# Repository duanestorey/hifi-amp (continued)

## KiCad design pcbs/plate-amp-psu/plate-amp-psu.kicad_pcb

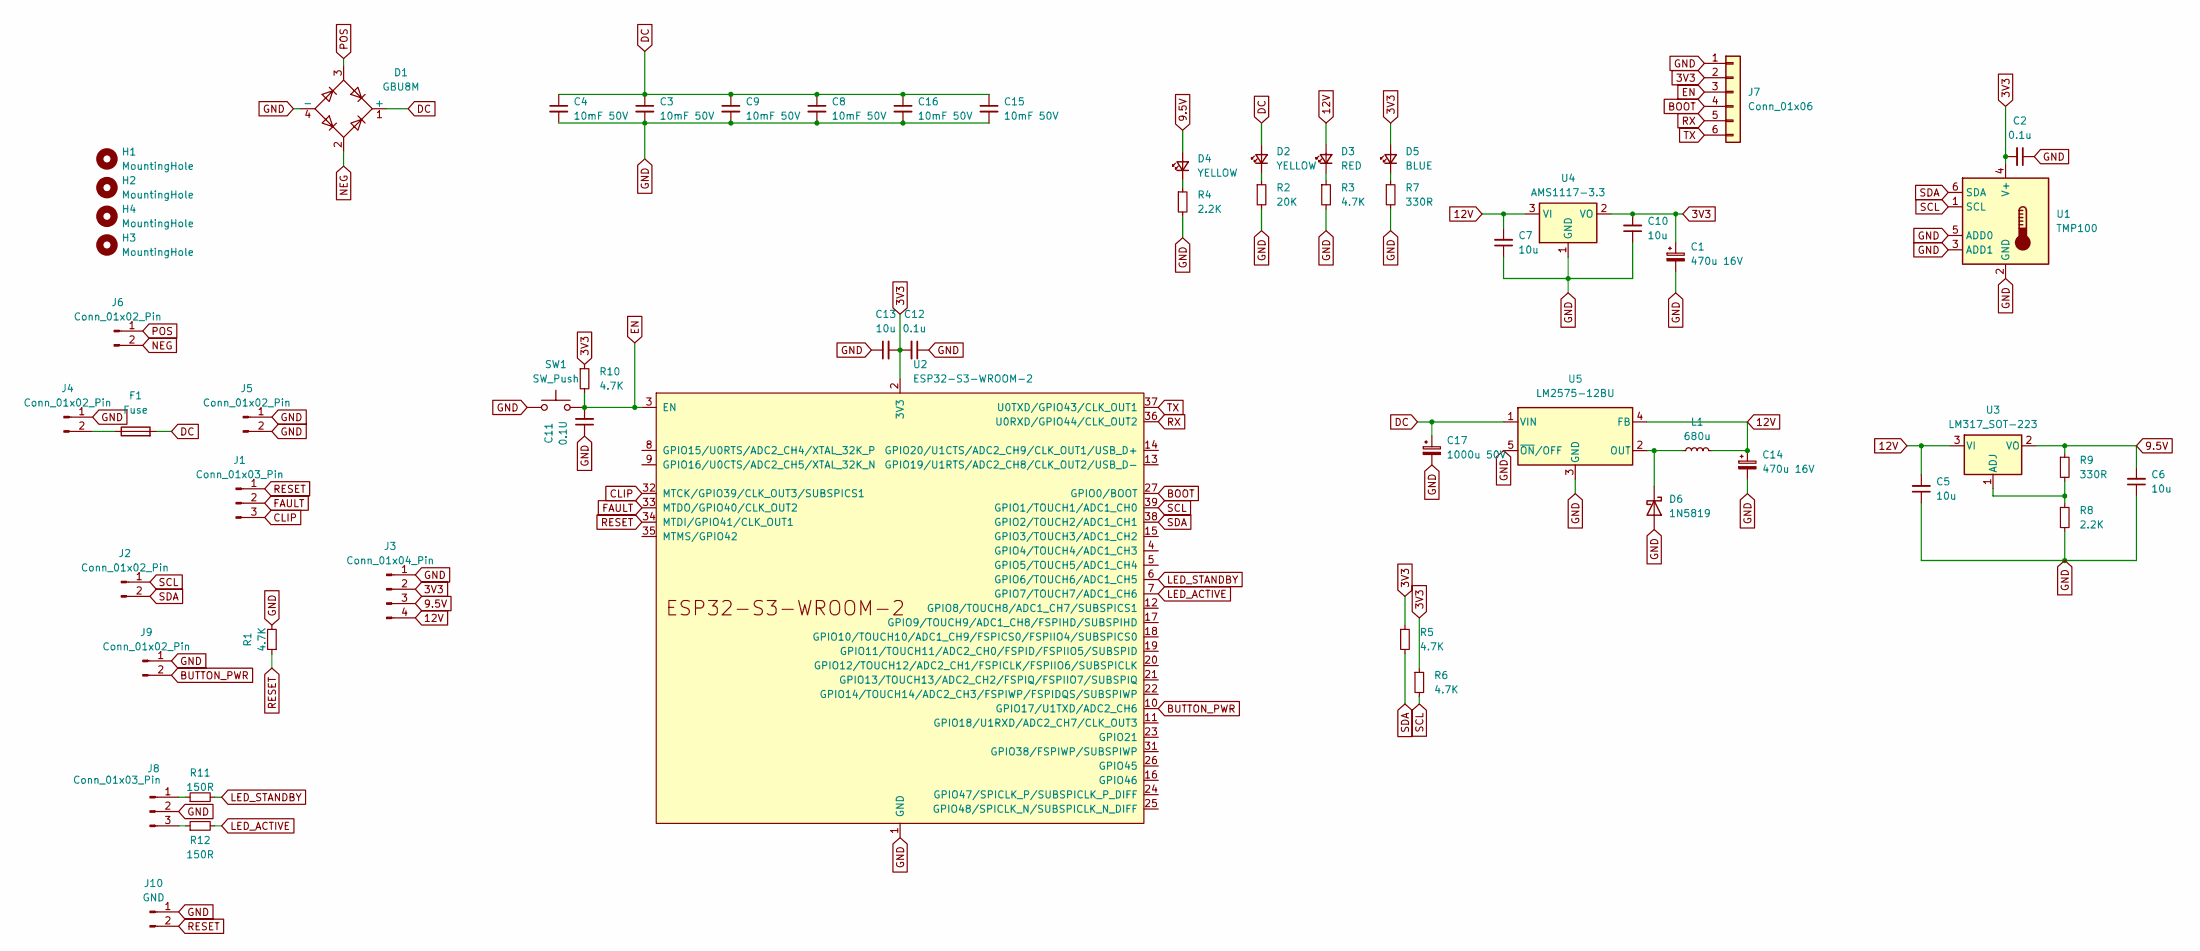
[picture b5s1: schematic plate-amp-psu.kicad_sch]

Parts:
C1, C14: 470u 16V; CP_Radial_D8.0mm_P3.50mm
C2, C12: 0.1u; C_0805_2012Metric_Pad1.18x1.45mm_HandSolder
C3, C4, C8, C9, C15, C16: 10mF 50V; CP_Radial_D25.0mm_P10.00mm_SnapIn
C5, C6, C7, C10, C13: 10u; C_1206_3216Metric_Pad1.33x1.80mm_HandSolder
C11: 0.1U; C_0805_2012Metric_Pad1.18x1.45mm_HandSolder
C17: 1000u 50V; CP_Radial_D12.5mm_P5.00mm
D1: GBU8M; Diode_Bridge_Vishay_GBU
D2, D4: YELLOW; LED_0805_2012Metric_Pad1.15x1.40mm_HandSolder
D3: RED; LED_0805_2012Metric_Pad1.15x1.40mm_HandSolder
D5: BLUE; LED_0805_2012Metric_Pad1.15x1.40mm_HandSolder
D6: 1N5819; D_DO-41_SOD81_P7.62mm_Horizontal; Mouser 863-MBR150RLG
F1: Fuse; Aliexpress Fuse 5x20
H1, H2, H3, H4: MountingHole; MountingHole_3.2mm_M3_DIN965_Pad_TopBottom
J1, J8: Conn_01x03_Pin; JST_PH_B3B-PH-K_1x03_P2.00mm_Vertical
J2, J9: Conn_01x02_Pin; JST_PH_B2B-PH-K_1x02_P2.00mm_Vertical
J3: Conn_01x04_Pin; JST_PH_B4B-PH-K_1x04_P2.00mm_Vertical
J4, J5: Conn_01x02_Pin; JST_VH_B2P-VH-B_1x02_P3.96mm_Vertical
J6: Conn_01x02_Pin; TerminalBlock_MetzConnect_Type059_RT06302HBWC_1x02_P3.50mm_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
J7: Conn_01x06; PinHeader_1x06_P2.54mm_Vertical
J10: GND; JST_PH_B2B-PH-K_1x02_P2.00mm_Vertical
L1: 680u; L_Changjiang_FXL1365; Mouser 710-7447709681
R1, R3, R5, R6, R10: 4.7K; R_0603_1608Metric_Pad0.98x0.95mm_HandSolder
R2: 20K; R_0603_1608Metric_Pad0.98x0.95mm_HandSolder
R4, R8: 2.2K; R_0603_1608Metric_Pad0.98x0.95mm_HandSolder
R7, R9: 330R; R_0603_1608Metric_Pad0.98x0.95mm_HandSolder
R11, R12: 150R; R_0603_1608Metric_Pad0.98x0.95mm_HandSolder
SW1: SW_Push; Button Aliexpress 4x4
U1: TMP100; SOT-23-6
U2: ESP32-S3-WROOM-2
U3: LM317_SOT-223; SOT-223-3_TabPin2
U4: AMS1117-3.3; SOT-223-3_TabPin2
U5: LM2575-12BU; TO-263-5_TabPin3; Mouser TL2575HV-12IKTTR

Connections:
3V3: C1.1, C2.2, C10.2, C12.2, C13.2, D5.2 (A), J3.2, J7.2, R5.1, R6.1, R10.1, U1.4 (V+), U2.2 (3V3), U4.2 (VO)
9.5V: C6.2, D4.2 (A), J3.3, R9.1, U3.2 (VO)
12V: C5.2, C7.2, C14.1, D3.2 (A), J3.4, L1.2, U3.3 (VI), U4.3 (VI), U5.4 (FB)
BOOT: J7.4, U2.27 (GPIO0/BOOT)
BUTTON_PWR: J9.2, U2.10 (GPIO17/U1TXD/ADC2_CH6)
CLIP: J1.3, U2.32 (MTCK/GPIO39/CLK_OUT3/SUBSPICS1)
DC: C3.1, C4.1, C8.1, C9.1, C15.1, C16.1, C17.1, D1.1 (+), D2.2 (A), F1.2, U5.1 (VIN)
EN: C11.2, J7.3, R10.2, SW1.2, U2.3 (EN)
FAULT: J1.2, U2.33 (MTDO/GPIO40/CLK_OUT2)
GND: C1.2, C2.1, C3.2, C4.2, C5.1, C6.1, C7.1, C8.2, C9.2, C10.1, C11.1, C12.1, C13.1, C14.2, C15.2, C16.2, C17.2, D1.4 (-), D6.2 (A), J3.1, J4.1, J5.1, J5.2, J7.1, J8.2, J9.1, J10.1, R1.2, R2.2, R3.2, R4.2, R7.2, R8.2, SW1.1, U1.2 (GND), U1.3 (ADD1), U1.5 (ADD0), U2.1 (GND), U2.40 (GND), U2.41 (GND), U4.1 (GND), U5.3 (GND), U5.5 (~ON/OFF)
LED_ACTIVE: R12.2, U2.7 (GPIO7/TOUCH7/ADC1_CH6)
LED_STANDBY: R11.2, U2.6 (GPIO6/TOUCH6/ADC1_CH5)
NEG: D1.2, J6.2
unnamed: D2.1 (K), R2.1
unnamed: D3.1 (K), R3.1
unnamed: D4.1 (K), R4.1
unnamed: D5.1 (K), R7.1
unnamed: D6.1 (K), L1.1, U5.2 (OUT)
unnamed: F1.1, J4.2
unnamed: J8.1, R11.1
unnamed: J8.3, R12.1
unnamed: R8.1, R9.2, U3.1 (ADJ)
POS: D1.3, J6.1
RESET: J1.1, J10.2, R1.1, U2.34 (MTDI/GPIO41/CLK_OUT1)
RX: J7.5, U2.36 (U0RXD/GPIO44/CLK_OUT2)
SCL: J2.1, R6.2, U1.1 (SCL), U2.39 (GPIO1/TOUCH1/ADC1_CH0)
SDA: J2.2, R5.2, U1.6 (SDA), U2.38 (GPIO2/TOUCH2/ADC1_CH1)
TX: J7.6, U2.37 (U0TXD/GPIO43/CLK_OUT1)

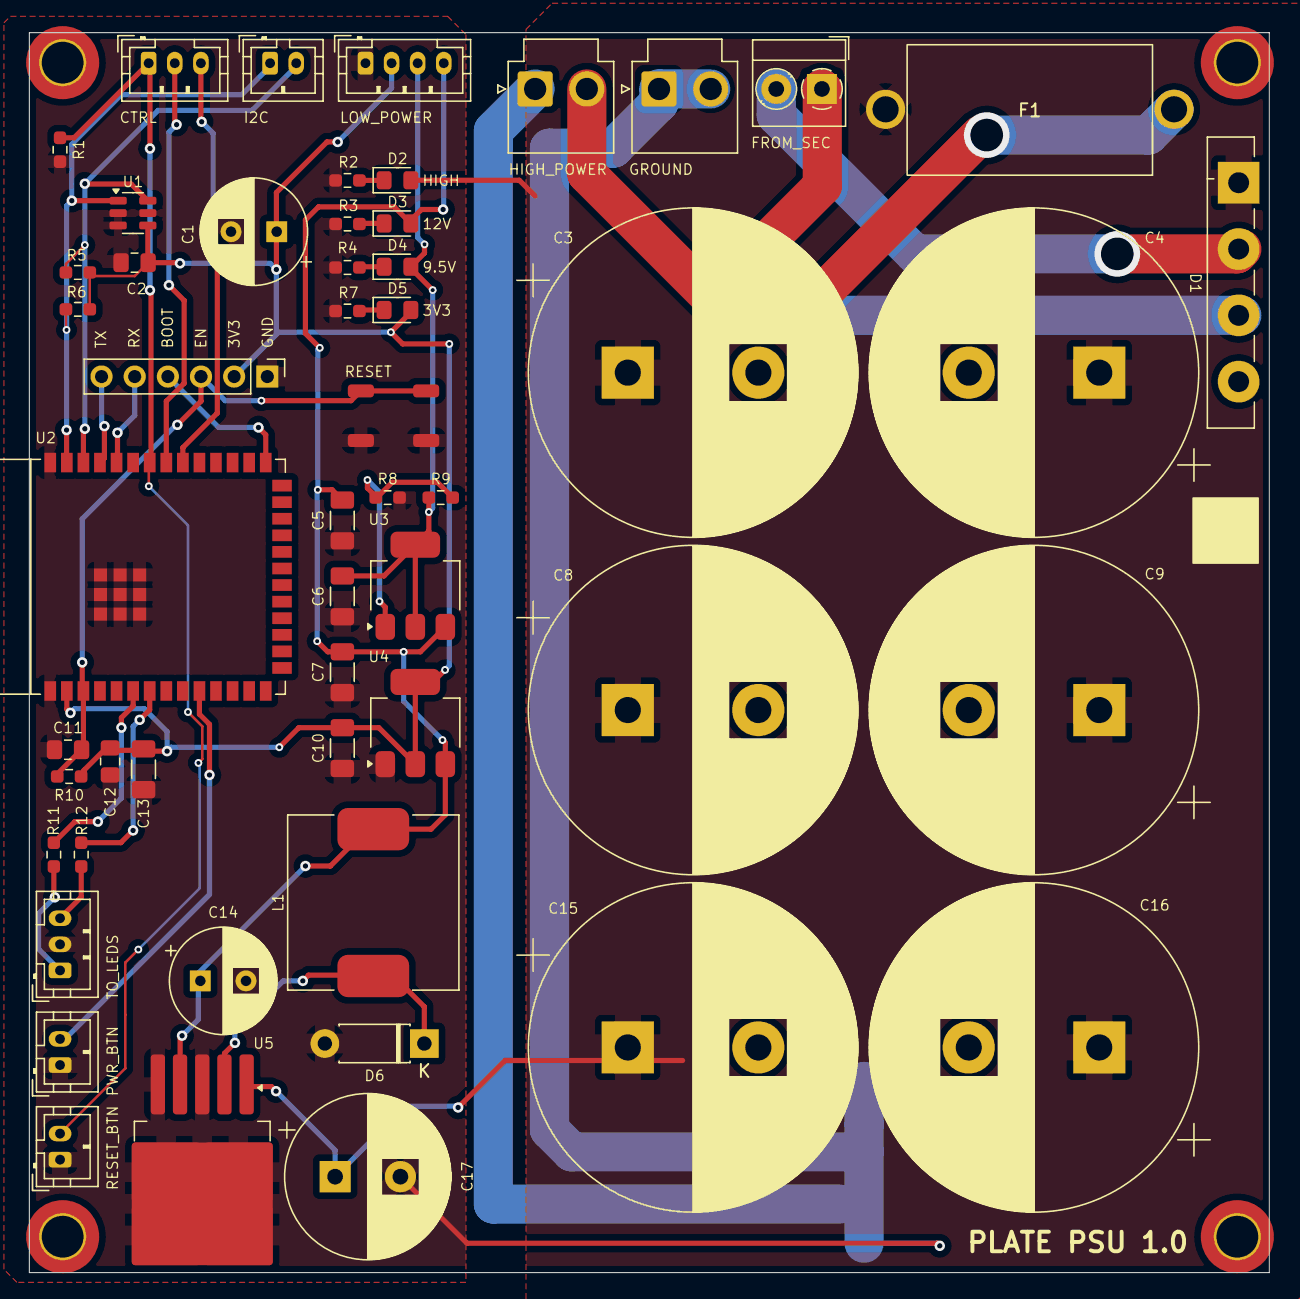
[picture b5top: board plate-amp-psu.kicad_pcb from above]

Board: 2 copper layers, 95.0 x 95.0 mm, 57 parts (0 on the bottom side), 28 nets.

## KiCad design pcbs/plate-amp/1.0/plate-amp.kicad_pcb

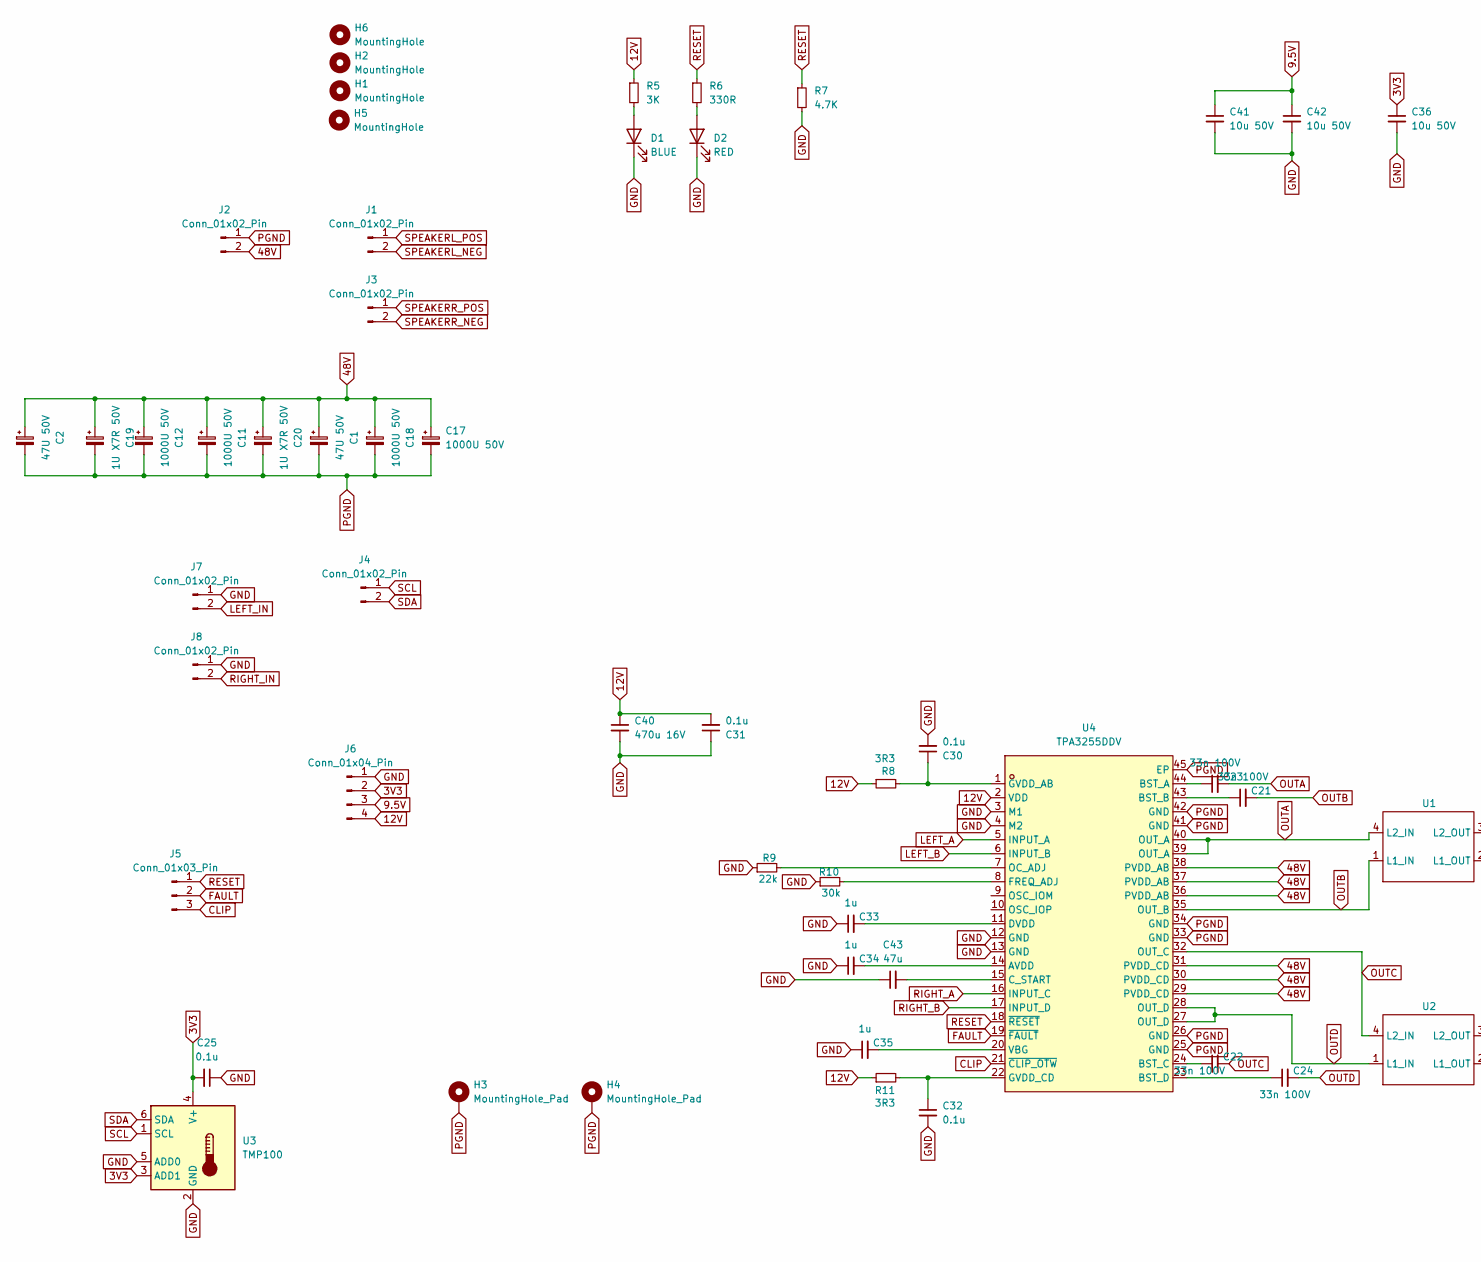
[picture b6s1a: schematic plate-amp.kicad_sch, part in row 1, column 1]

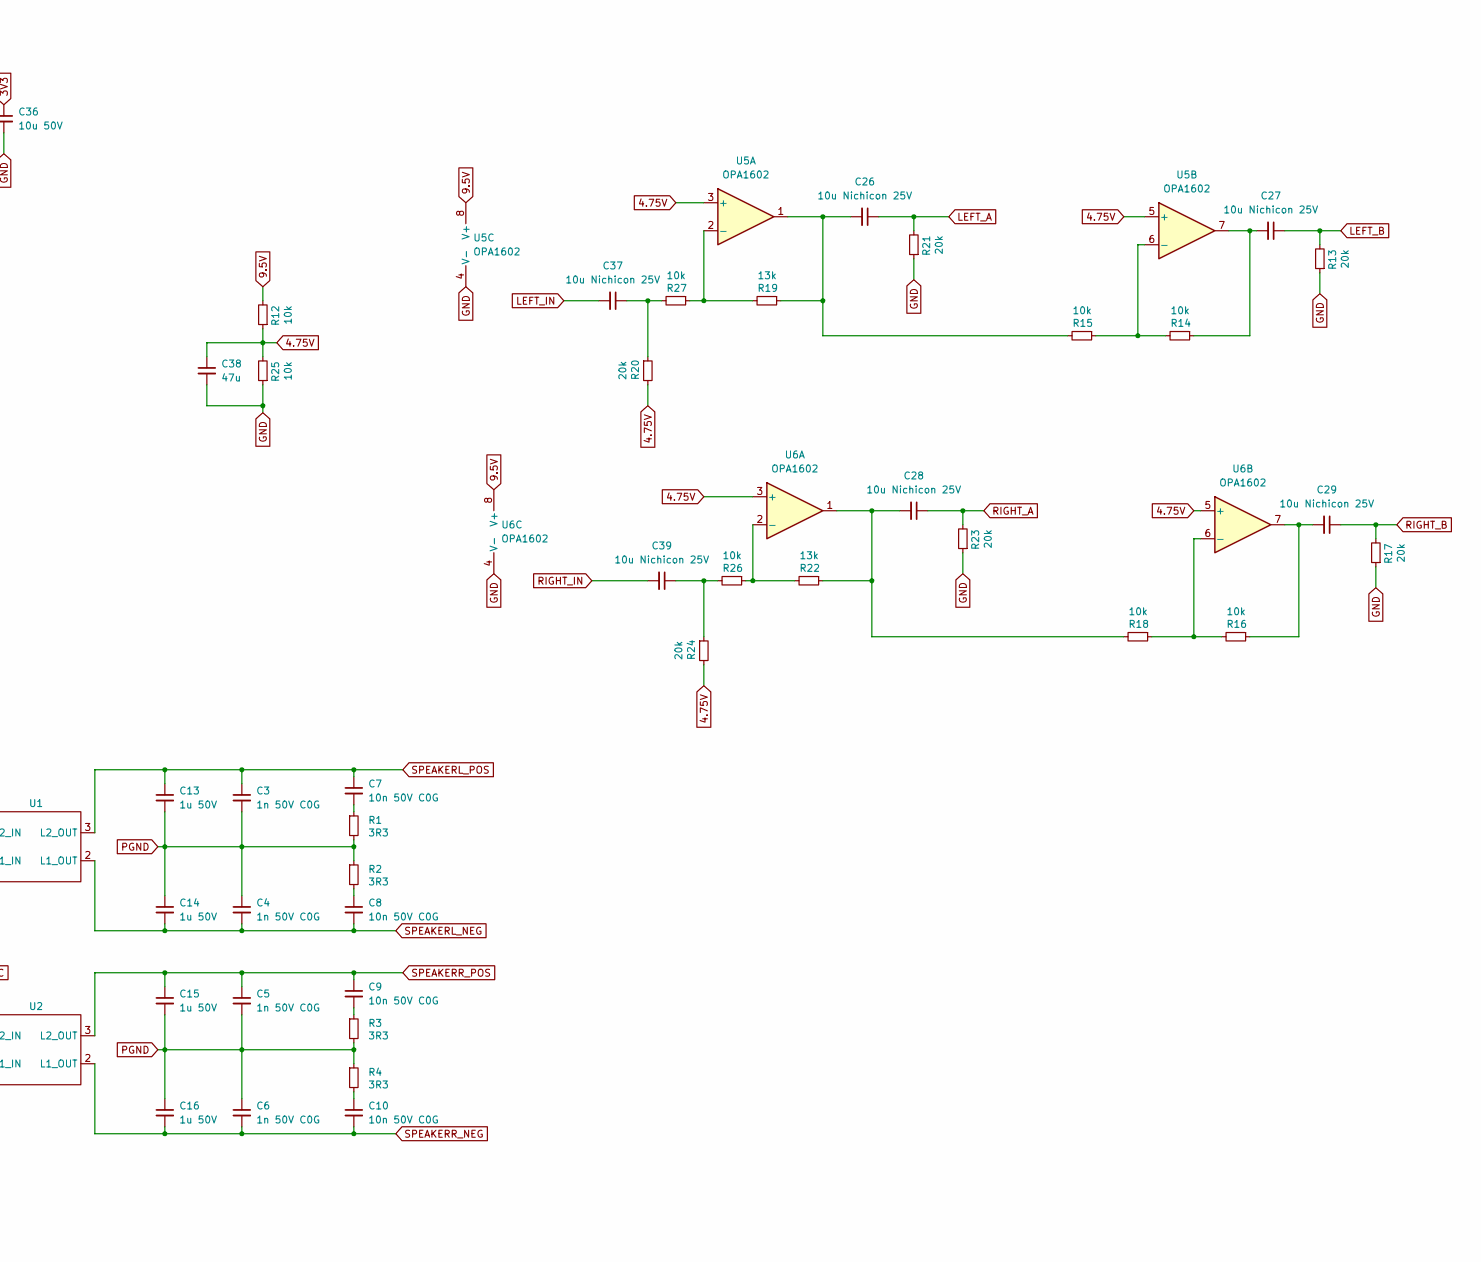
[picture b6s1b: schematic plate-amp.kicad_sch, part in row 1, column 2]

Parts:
C1, C2: 47U 50V; CP_Radial_D6.3mm_P2.50mm
C3, C4, C5, C6: 1n 50V C0G; C_1206_3216Metric_Pad1.33x1.80mm_HandSolder
C7, C8, C9, C10: 10n 50V C0G; C_1206_3216Metric_Pad1.33x1.80mm_HandSolder
C11, C12, C17, C18: 1000U 50V; CP_Radial_D12.5mm_P5.00mm
C13, C14, C15, C16: 1u 50V; CP_Radial_D5.0mm_P2.00mm
C19, C20: 1U X7R 50V; C_1206_3216Metric_Pad1.33x1.80mm_HandSolder; Mouser 80-C1206X475J5RACTU
C21, C22, C23, C24: 33n 100V; C_1206_3216Metric_Pad1.33x1.80mm_HandSolder
C25, C30, C31, C32: 0.1u; C_0805_2012Metric_Pad1.18x1.45mm_HandSolder
C26, C27, C28, C29, C37, C39: 10u Nichicon 25V; CP_Radial_D5.0mm_P2.50mm
C33, C34, C35: 1u; C_1206_3216Metric_Pad1.33x1.80mm_HandSolder
C36, C41, C42: 10u 50V; C_1206_3216Metric_Pad1.33x1.80mm_HandSolder
C38, C43: 47u; C_1206_3216Metric_Pad1.33x1.80mm_HandSolder
C40: 470u 16V; CP_Radial_D8.0mm_P3.50mm
D1: BLUE; LED_0603_1608Metric_Pad1.05x0.95mm_HandSolder; LCSC XL-1608UBC-04
D2: RED; LED_0603_1608Metric_Pad1.05x0.95mm_HandSolder; LCSC XL-1608UBC-04
H1, H2, H5, H6: MountingHole; MountingHole_3.2mm_M3_DIN965_Pad_TopOnly
H3, H4: MountingHole_Pad; MountingHole_3.2mm_M3_DIN965_Pad_TopBottom
J1, J2, J3: Conn_01x02_Pin; JST_VH_B2P-VH-B_1x02_P3.96mm_Vertical
J4, J7, J8: Conn_01x02_Pin; JST_PH_B2B-PH-K_1x02_P2.00mm_Vertical
J5: Conn_01x03_Pin; JST_PH_B3B-PH-K_1x03_P2.00mm_Vertical
J6: Conn_01x04_Pin; JST_PH_B4B-PH-K_1x04_P2.00mm_Vertical
R1, R2, R3, R4: 3R3; R_2512_6332Metric_Pad1.40x3.35mm_HandSolder
R5: 3K; R_0603_1608Metric_Pad0.98x0.95mm_HandSolder
R6: 330R; R_0603_1608Metric_Pad0.98x0.95mm_HandSolder
R7: 4.7K; R_0603_1608Metric_Pad0.98x0.95mm_HandSolder
R8, R11: 3R3; C_0603_1608Metric_Pad1.08x0.95mm_HandSolder
R9: 22k; C_0603_1608Metric_Pad1.08x0.95mm_HandSolder
R10: 30k; C_0603_1608Metric_Pad1.08x0.95mm_HandSolder
R12, R14, R15, R16, R18, R25, R26, R27: 10k; C_0603_1608Metric_Pad1.08x0.95mm_HandSolder
R13, R17, R20, R21, R23, R24: 20k; C_0603_1608Metric_Pad1.08x0.95mm_HandSolder
R19, R22: 13k; C_0603_1608Metric_Pad1.08x0.95mm_HandSolder
U1, U2: UA8014-AL
U3: TMP100; SOT-23-6
U4: TPA3255DDV; HTSSOP-44_L14.0-W6.1-P0.64-LS8.1-BL-EP; LCSC Part C2879299
U5, U6: OPA1602; SOIC-8_3.9x4.9mm_P1.27mm

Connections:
3V3: C25.2, C36.1, J6.2, U3.3 (ADD1), U3.4 (V+)
4.75V: C38.1, R12.1, R20.2, R24.2, R25.2, U5.3 (+), U5.5 (+), U6.3 (+), U6.5 (+)
9.5V: C41.1, C42.1, J6.3, R12.2, U5.8 (V+), U6.8 (V+)
12V: C31.2, C40.1, J6.4, R5.1, R8.1, R11.1, U4.2 (VDD)
48V: C1.1, C2.1, C11.1, C12.1, C17.1, C18.1, C19.1, C20.1, J2.2, U4.29 (PVDD_CD), U4.30 (PVDD_CD), U4.31 (PVDD_CD), U4.36 (PVDD_AB), U4.37 (PVDD_AB), U4.38 (PVDD_AB)
CLIP: J5.3, U4.21 (~CLIP_OTW)
FAULT: J5.2, U4.19 (~FAULT)
GND: C25.1, C30.2, C31.1, C32.2, C33.1, C34.1, C35.1, C36.2, C38.2, C40.2, C41.2, C42.2, C43.1, D1.1 (K), D2.1 (K), J6.1, J7.1, J8.1, R7.2, R9.1, R10.1, R13.1, R17.1, R21.1, R23.1, R25.1, U3.2 (GND), U3.5 (ADD0), U4.3 (M1), U4.4 (M2), U4.12 (GND), U4.13 (GND), U5.4 (V-), U6.4 (V-)
LEFT_A: C26.1, R21.2, U4.5 (INPUT_A)
LEFT_B: C27.1, R13.2, U4.6 (INPUT_B)
LEFT_IN: C37.2, J7.2
unnamed: C7.2, R1.1
unnamed: C8.1, R2.2
unnamed: C9.2, R3.1
unnamed: C10.1, R4.2
unnamed: C26.2, R15.2, R19.1, U5.1
unnamed: C27.2, R14.1, U5.7
unnamed: C28.2, R18.2, R22.1, U6.1
unnamed: C29.2, R16.1, U6.7
unnamed: C37.1, R20.1, R27.2
unnamed: C39.1, R24.1, R26.2
unnamed: D1.2 (A), R5.2
unnamed: D2.2 (A), R6.2
unnamed: C34.2, U4.14 (AVDD)
unnamed: C23.1, U4.44 (BST_A)
unnamed: C21.1, U4.43 (BST_B)
unnamed: C22.1, U4.24 (BST_C)
unnamed: C24.1, U4.23 (BST_D)
unnamed: C43.2, U4.15 (C_START)
unnamed: C33.2, U4.11 (DVDD)
unnamed: R10.2, U4.8 (FREQ_ADJ)
unnamed: C30.1, R8.2, U4.1 (GVDD_AB)
unnamed: C32.1, R11.2, U4.22 (GVDD_CD)
unnamed: R9.2, U4.7 (OC_ADJ)
unnamed: C35.2, U4.20 (VBG)
unnamed: R19.2, R27.1, U5.2 (-)
unnamed: R14.2, R15.1, U5.6 (-)
unnamed: R22.2, R26.1, U6.2 (-)
unnamed: R16.2, R18.1, U6.6 (-)
OUTA: C23.2, U1.4 (L2_IN), U4.39 (OUT_A), U4.40 (OUT_A)
OUTB: C21.2, U1.1 (L1_IN), U4.35 (OUT_B)
OUTC: C22.2, U2.4 (L2_IN), U4.32 (OUT_C)
OUTD: C24.2, U2.1 (L1_IN), U4.27 (OUT_D), U4.28 (OUT_D)
PGND: C1.2, C2.2, C3.2, C4.1, C5.2, C6.1, C11.2, C12.2, C13.2, C14.1, C15.2, C16.1, C17.2, C18.2, C19.2, C20.2, H3.1, H4.1, J2.1, R1.2, R2.1, R3.2, R4.1, U4.25 (GND), U4.26 (GND), U4.33 (GND), U4.34 (GND), U4.41 (GND), U4.42 (GND), U4.45 (EP)
RESET: J5.1, R6.1, R7.1, U4.18 (~RESET)
RIGHT_A: C28.1, R23.2, U4.16 (INPUT_C)
RIGHT_B: C29.1, R17.2, U4.17 (INPUT_D)
RIGHT_IN: C39.2, J8.2
SCL: J4.1, U3.1 (SCL)
SDA: J4.2, U3.6 (SDA)
SPEAKERL_NEG: C4.2, C8.2, C14.2, J1.2, U1.2 (L1_OUT)
SPEAKERL_POS: C3.1, C7.1, C13.1, J1.1, U1.3 (L2_OUT)
SPEAKERR_NEG: C6.2, C10.2, C16.2, J3.2, U2.2 (L1_OUT)
SPEAKERR_POS: C5.1, C9.1, C15.1, J3.1, U2.3 (L2_OUT)

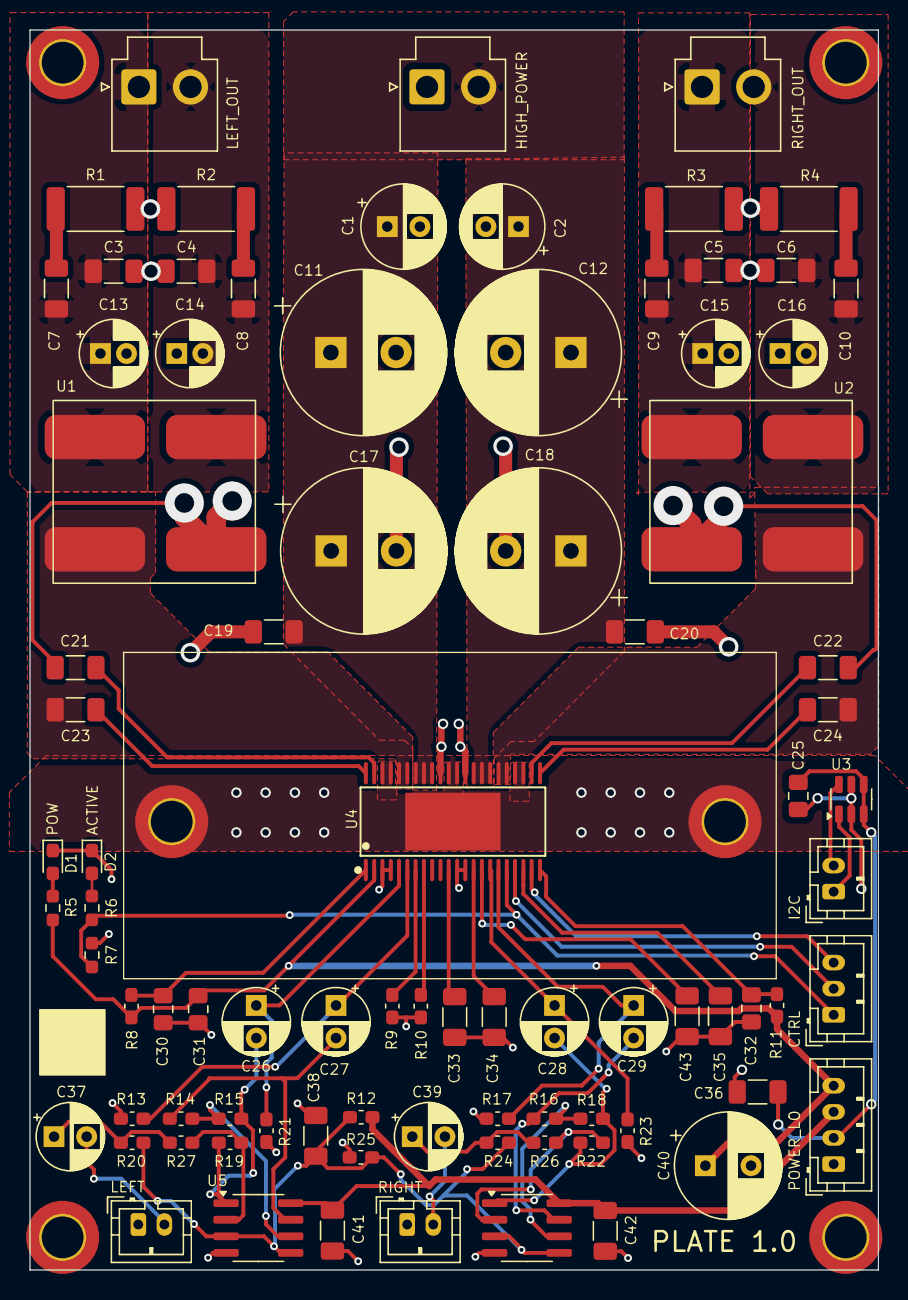
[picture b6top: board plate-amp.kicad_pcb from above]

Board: 2 copper layers, 65.0 x 95.0 mm, 92 parts (0 on the bottom side), 54 nets.
